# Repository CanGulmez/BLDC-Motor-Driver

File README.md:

# 2kW BLDC Motor Driver

This project was created for Teknofest - Efficiency Challenge Competition

This repository consists of two part. First is the motor dirver firmware
and second is the KiCAD design. In firmware development, I've used VS Code
and PlatformIO plugin. PCB design is based on STM32F44RE microcontroller
so that the firmware was written with STM32 HAL (Hardware Abstraction Layer)
library. KiCAD design includes both schematic and PCB layout so that it 
can be used directly.

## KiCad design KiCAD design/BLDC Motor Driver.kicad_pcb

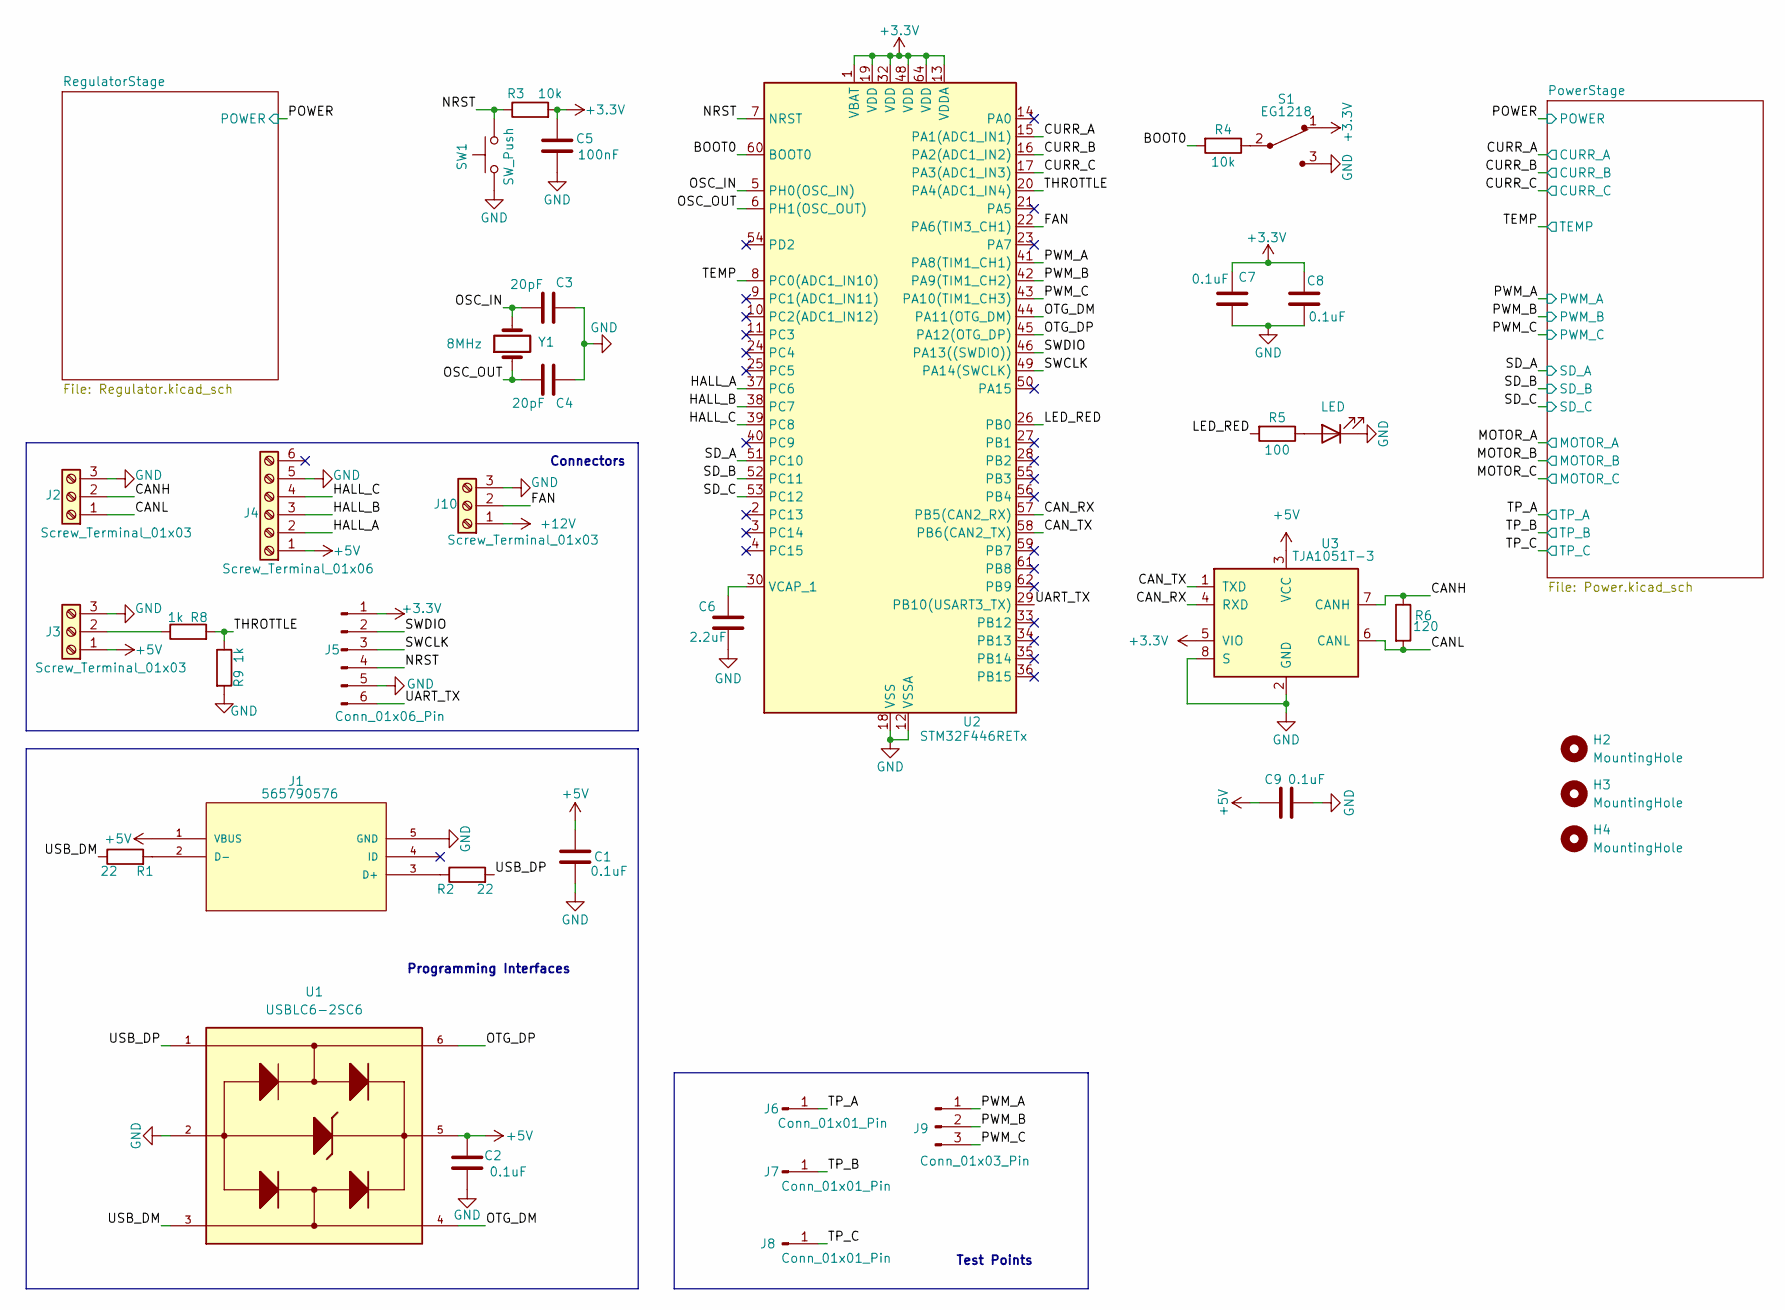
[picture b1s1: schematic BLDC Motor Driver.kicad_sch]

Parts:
C1, C2, C7, C8, C9: 0.1uF; C_0603_1608Metric
C3, C4: 20pF; C_0603_1608Metric
C5: 100nF; C_0603_1608Metric
C6: 2.2uF; C_0805_2012Metric
D1: LED; LED_0603_1608Metric
H2, H3, H4: MountingHole; MountingHole_3.2mm_M3
J1: 565790576; 56579-0576_MOL; MANUFACTURER_PART_NUMBER 565790576
J2, J3, J10: Screw_Terminal_01x03; TerminalBlock_Phoenix_MKDS-1,5-3-5.08_1x03_P5.08mm_Horizont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
J4: Screw_Terminal_01x06; TerminalBlock_Phoenix_MKDS-1,5-6-5.08_1x06_P5.08mm_Horizont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
J5: Conn_01x06_Pin; PinHeader_1x06_P2.54mm_Vertical
J6, J7, J8: Conn_01x01_Pin; PinHeader_1x01_P2.54mm_Vertical
J9: Conn_01x03_Pin; PinHeader_1x03_P2.54mm_Vertical
R1, R2: 22; R_0603_1608Metric
R3, R4: 10k; R_0603_1608Metric
R5: 100; R_0603_1608Metric
R6: 120; R_0603_1608Metric
R8, R9: 1k; R_0603_1608Metric
S1: EG1218; Switch_Slide_11.6x4mm_EG1218; MPN EG1218; Digi-Key_PN EG1903-ND
SW1: SW_Push; SW_SPST_B3U-1000P
U1: USBLC6-2SC6; SOT95P280X145-6N
U2: STM32F446RETx; LQFP-64_10x10mm_P0.5mm
U3: TJA1051T-3; SOIC-8_3.9x4.9mm_P1.27mm
Y1: 8MHz; Crystal_SMD_5032-2Pin_5.0x3.2mm

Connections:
+3.3V: C5.1, C7.1, C8.1, J5.1, R3.2, S1.1, U2.1 (VBAT), U2.13 (VDDA), U2.19 (VDD), U2.32 (VDD), U2.48 (VDD), U2.64 (VDD), U3.5 (VIO); also elsewhere on the board
+5V: C1.1, C2.1, C9.1, J1.1 (VBUS), J3.1, J4.1, U1.5, U3.3 (VCC); also elsewhere on the board
+12V: J10.1; also elsewhere on the board
/BOOT0: R4.2, U2.60 (BOOT0)
/CANH: J2.2, R6.1, U3.7 (CANH)
/CANL: J2.1, R6.2, U3.6 (CANL)
/CAN_RX: U2.57 (PB5(CAN2_RX)), U3.4 (RXD)
/CAN_TX: U2.58 (PB6(CAN2_TX)), U3.1 (TXD)
/CURR_A: U2.15 (PA1(ADC1_IN1)); also elsewhere on the board
/CURR_B: U2.16 (PA2(ADC1_IN2)); also elsewhere on the board
/CURR_C: U2.17 (PA3(ADC1_IN3)); also elsewhere on the board
/FAN: J10.2, U2.22 (PA6(TIM3_CH1))
/HALL_A: J4.2, U2.37 (PC6)
/HALL_B: J4.3, U2.38 (PC7)
/HALL_C: J4.4, U2.39 (PC8)
/LED_RED: R5.2, U2.26 (PB0)
/NRST: J5.4, R3.1, SW1.2, U2.7 (NRST)
/OSC_IN: C3.1, U2.5 (PH0(OSC_IN)), Y1.2
/OSC_OUT: C4.1, U2.6 (PH1(OSC_OUT)), Y1.1
/OTG_DM: U1.4, U2.44 (PA11(OTG_DM))
/OTG_DP: U1.6, U2.45 (PA12(OTG_DP))
/PWM_A: J9.1, U2.41 (PA8(TIM1_CH1)); also elsewhere on the board
/PWM_B: J9.2, U2.42 (PA9(TIM1_CH2)); also elsewhere on the board
/PWM_C: J9.3, U2.43 (PA10(TIM1_CH3)); also elsewhere on the board
/SD_A: U2.51 (PC10); also elsewhere on the board
/SD_B: U2.52 (PC11); also elsewhere on the board
/SD_C: U2.53 (PC12); also elsewhere on the board
/SWCLK: J5.3, U2.49 (PA14(SWCLK))
/SWDIO: J5.2, U2.46 (PA13((SWDIO)))
/TEMP: U2.8 (PC0(ADC1_IN10)); also elsewhere on the board
/THROTTLE: R8.2, R9.1, U2.20 (PA4(ADC1_IN4))
/TP_A: J6.1; also elsewhere on the board
/TP_B: J7.1; also elsewhere on the board
/TP_C: J8.1; also elsewhere on the board
/UART_TX: J5.6, U2.29 (PB10(USART3_TX))
/USB_DM: R1.1, U1.3
/USB_DP: R2.2, U1.1
GND: C1.2, C2.2, C3.2, C4.2, C5.2, C6.2, C7.2, C8.2, C9.2, D1.1 (K), J1.5 (GND), J2.3, J3.3, J4.5, J5.5, J10.3, R9.2, S1.3, SW1.1, U1.2, U2.12 (VSSA), U2.18 (VSS), U2.31 (VSS), U2.47 (VSS), U2.63 (VSS), U3.2 (GND), U3.8 (S); also elsewhere on the board
unnamed: D1.2 (A), R5.1
unnamed: J1.3 (D+), R2.1
unnamed: J1.2 (D-), R1.2
unnamed: J3.2, R8.1
unnamed: R4.1, S1.2
unnamed: C6.1, U2.30 (VCAP_1)

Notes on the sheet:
Connectors
Test Points
Programming Interfaces

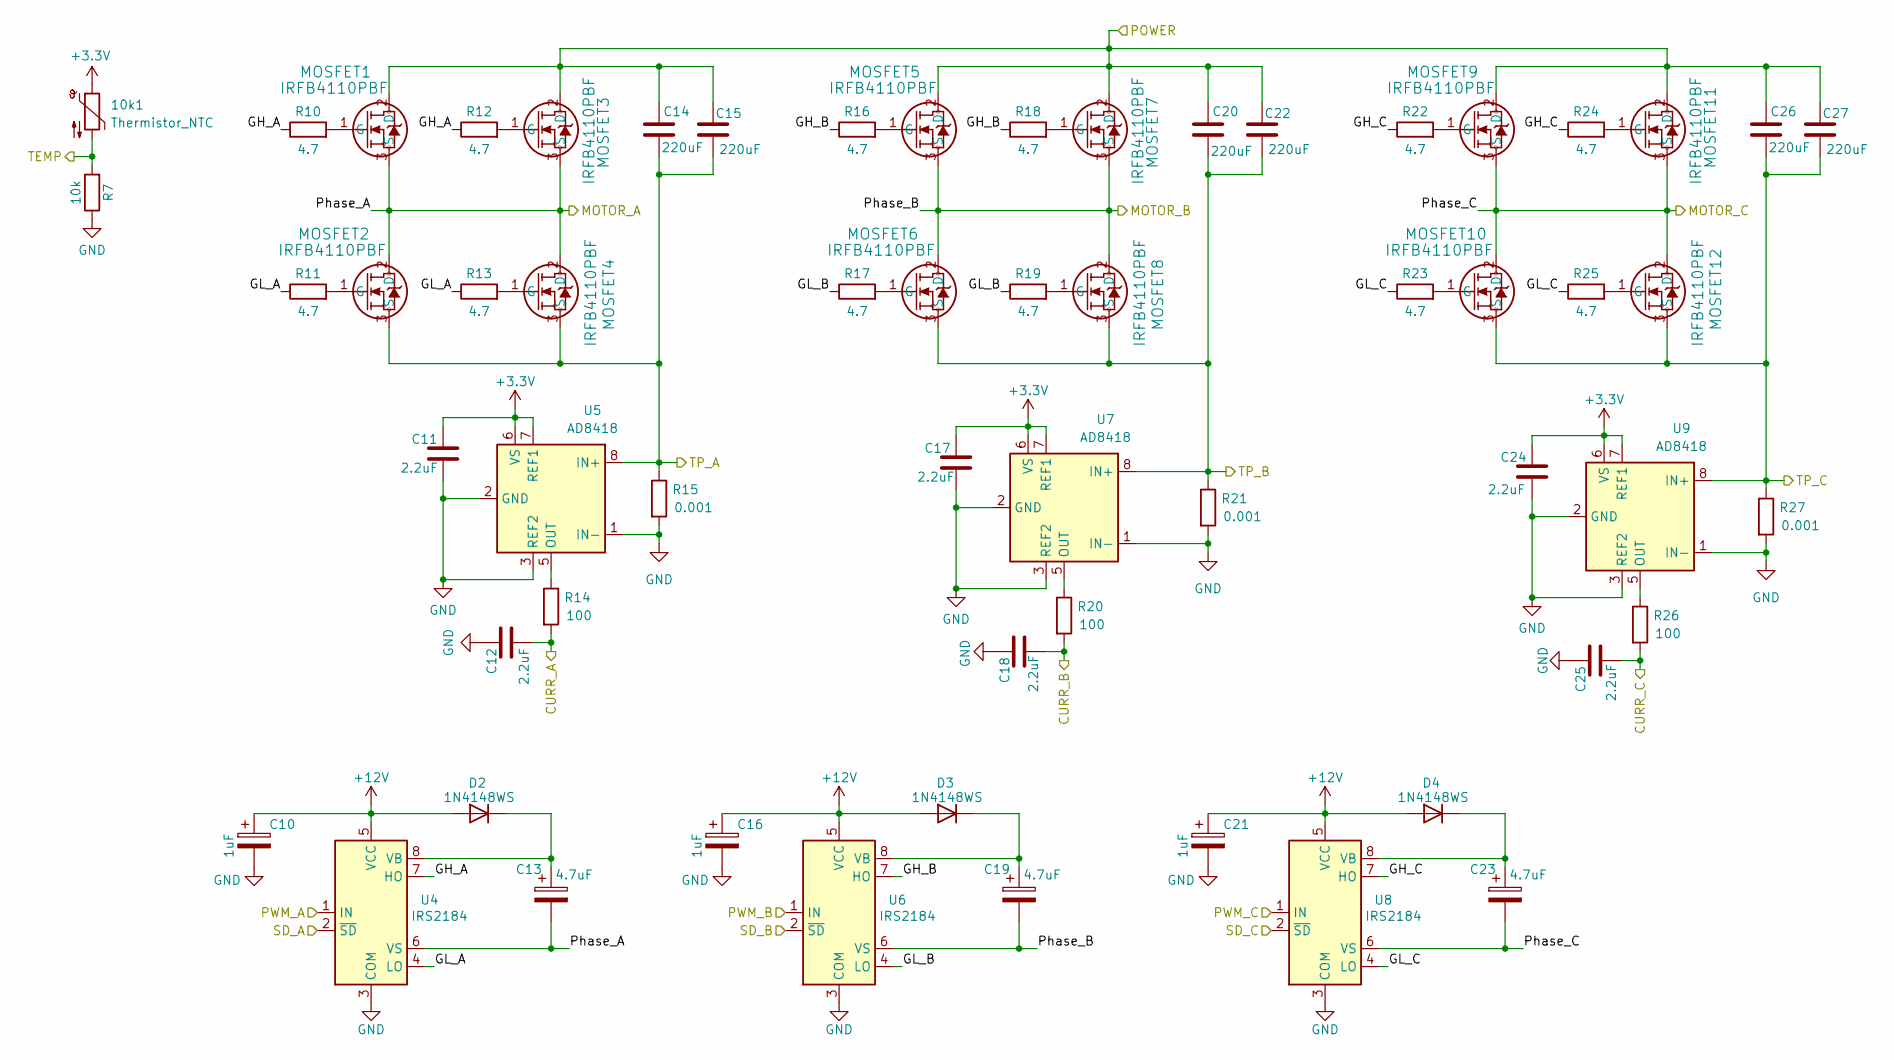
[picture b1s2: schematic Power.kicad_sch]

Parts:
10k1: Thermistor_NTC; R_0805_2012Metric
C10, C16, C21: 1uF; C_0805_2012Metric
C11, C12, C17, C18, C24, C25: 2.2uF; C_0805_2012Metric
C13, C19, C23: 4.7uF; C_0805_2012Metric
C14, C15, C20, C22, C26, C27: 220uF; C_Elec_10x10.2
D2, D3, D4: 1N4148WS; D_SOD-323
MOSFET1, MOSFET2, MOSFET3, MOSFET4, MOSFET5, MOSFET6, MOSFET7, MOSFET8, MOSFET9, MOSFET10, MOSFET11, MOSFET12: IRFB4110PBF; TO-220-3_Vertical
R7: 10k; R_0603_1608Metric
R10, R11, R12, R13, R16, R17, R18, R19, R22, R23, R24, R25: 4.7; R_0603_1608Metric
R14, R20, R26: 100; R_0603_1608Metric
R15, R21, R27: 0.001; R_2512_6332Metric
U4, U6, U8: IRS2184; SOIC-8_3.9x4.9mm_P1.27mm
U5, U7, U9: AD8418; SOIC-8_3.9x4.9mm_P1.27mm

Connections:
+3.3V: 10k1.1, C11.1, C17.1, C24.1, U5.6 (VS), U5.7 (REF1), U7.6 (VS), U7.7 (REF1), U9.6 (VS), U9.7 (REF1); also elsewhere on the board
+12V: C10.1, C16.1, C21.1, D2.2 (A), D3.2 (A), D4.2 (A), U4.5 (VCC), U6.5 (VCC), U8.5 (VCC); also elsewhere on the board
/CURR_A: C12.2, R14.2; also elsewhere on the board
/CURR_B: C18.2, R20.2; also elsewhere on the board
/CURR_C: C25.2, R26.2; also elsewhere on the board
/MOTOR_A: C13.2, MOSFET1.3 (S), MOSFET2.2 (D), MOSFET3.3 (S), MOSFET4.2 (D), U4.6 (VS)
/MOTOR_B: C19.2, MOSFET5.3 (S), MOSFET6.2 (D), MOSFET7.3 (S), MOSFET8.2 (D), U6.6 (VS)
/MOTOR_C: C23.2, MOSFET9.3 (S), MOSFET10.2 (D), MOSFET11.3 (S), MOSFET12.2 (D), U8.6 (VS)
/POWER: C14.1, C15.1, C20.1, C22.1, C26.1, C27.1, MOSFET1.2 (D), MOSFET3.2 (D), MOSFET5.2 (D), MOSFET7.2 (D), MOSFET9.2 (D), MOSFET11.2 (D); also elsewhere on the board
/PWM_A: U4.1 (IN); also elsewhere on the board
/PWM_B: U6.1 (IN); also elsewhere on the board
/PWM_C: U8.1 (IN); also elsewhere on the board
/PowerStage/GH_A: R10.1, R12.1, U4.7 (HO)
/PowerStage/GH_B: R16.1, R18.1, U6.7 (HO)
/PowerStage/GH_C: R22.1, R24.1, U8.7 (HO)
/PowerStage/GL_A: R11.1, R13.1, U4.4 (LO)
/PowerStage/GL_B: R17.1, R19.1, U6.4 (LO)
/PowerStage/GL_C: R23.1, R25.1, U8.4 (LO)
/SD_A: U4.2 (~SD); also elsewhere on the board
/SD_B: U6.2 (~SD); also elsewhere on the board
/SD_C: U8.2 (~SD); also elsewhere on the board
/TEMP: 10k1.2, R7.2; also elsewhere on the board
/TP_A: C14.2, C15.2, MOSFET2.3 (S), MOSFET4.3 (S), R15.1, U5.8 (IN+); also elsewhere on the board
/TP_B: C20.2, C22.2, MOSFET6.3 (S), MOSFET8.3 (S), R21.1, U7.8 (IN+); also elsewhere on the board
/TP_C: C26.2, C27.2, MOSFET10.3 (S), MOSFET12.3 (S), R27.1, U9.8 (IN+); also elsewhere on the board
GND: C10.2, C11.2, C12.1, C16.2, C17.2, C18.1, C21.2, C24.2, C25.1, R7.1, R15.2, R21.2, R27.2, U4.3 (COM), U5.1 (IN-), U5.2 (GND), U5.3 (REF2), U6.3 (COM), U7.1 (IN-), U7.2 (GND), U7.3 (REF2), U8.3 (COM), U9.1 (IN-), U9.2 (GND), U9.3 (REF2); also elsewhere on the board
unnamed: C13.1, D2.1 (K), U4.8 (VB)
unnamed: C19.1, D3.1 (K), U6.8 (VB)
unnamed: C23.1, D4.1 (K), U8.8 (VB)
unnamed: MOSFET1.1 (G), R10.2
unnamed: MOSFET2.1 (G), R11.2
unnamed: MOSFET3.1 (G), R12.2
unnamed: MOSFET4.1 (G), R13.2
unnamed: MOSFET5.1 (G), R16.2
unnamed: MOSFET6.1 (G), R17.2
unnamed: MOSFET7.1 (G), R18.2
unnamed: MOSFET8.1 (G), R19.2
unnamed: MOSFET9.1 (G), R22.2
unnamed: MOSFET10.1 (G), R23.2
unnamed: MOSFET11.1 (G), R24.2
unnamed: MOSFET12.1 (G), R25.2
unnamed: R14.1, U5.5 (OUT)
unnamed: R20.1, U7.5 (OUT)
unnamed: R26.1, U9.5 (OUT)

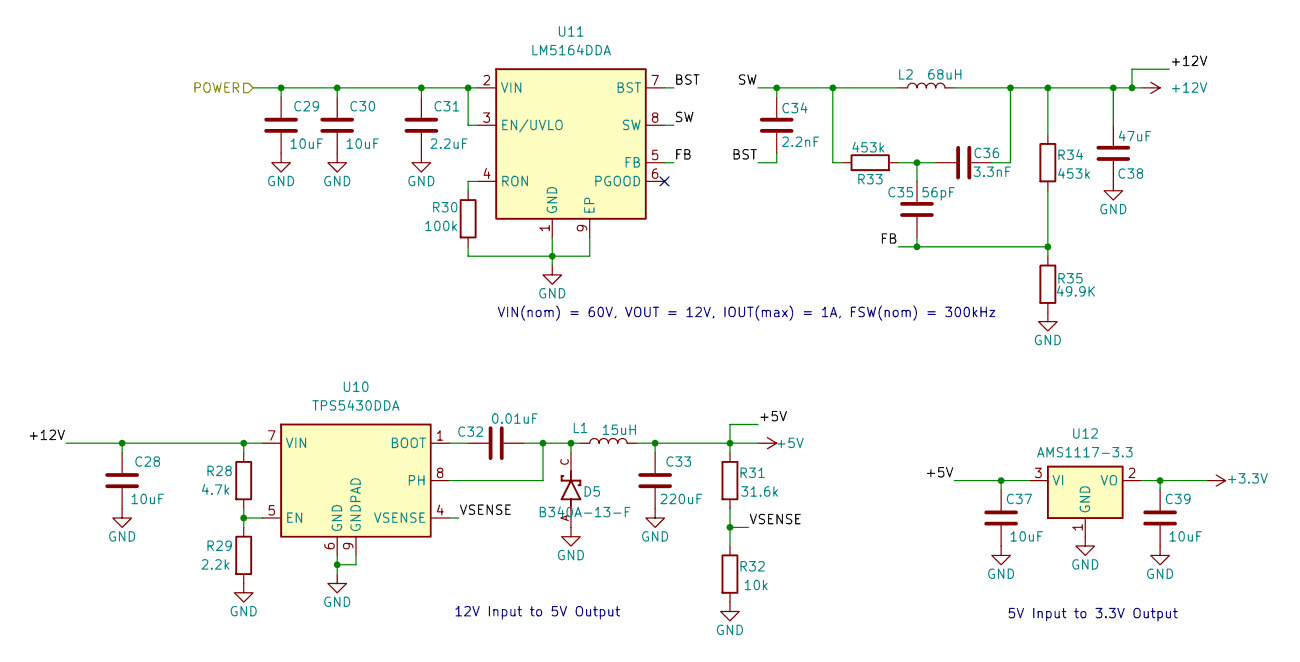
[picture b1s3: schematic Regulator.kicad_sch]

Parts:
C28, C29, C30, C37, C39: 10uF; C_0805_2012Metric
C31: 2.2uF; C_0805_2012Metric
C32: 0.01uF; C_0402_1005Metric
C33: 220uF; C_Elec_6.3x5.4
C34: 2.2nF; C_0402_1005Metric
C35: 56pF; C_0402_1005Metric
C36: 3.3nF; C_0402_1005Metric
C38: 47uF; C_Elec_8x6.2
D5: B340A-13-F; DIOM5226X240N; PARTREV 17-2
L1: 15uH; L_0805_2012Metric
L2: 68uH; L_6.3x6.3_H3
R28: 4.7k; R_0603_1608Metric
R29: 2.2k; R_0603_1608Metric
R30: 100k; R_0603_1608Metric
R31: 31.6k; R_0603_1608Metric
R32: 10k; R_0603_1608Metric
R33, R34: 453k; R_0603_1608Metric
R35: 49.9K; R_0603_1608Metric
U10: TPS5430DDA; TI_SO-PowerPAD-8_ThermalVias
U11: LM5164DDA; HSOP-8-1EP_3.9x4.9mm_P1.27mm_EP2.41x3.1mm_ThermalVias
U12: AMS1117-3.3; SOT-223-3_TabPin2

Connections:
+3.3V: C39.1, U12.2 (VO); also elsewhere on the board
+5V: C33.1, C37.1, L1.2, R31.1, U12.3 (VI); also elsewhere on the board
+12V: C28.1, C36.2, C38.2, L2.2, R28.1, R34.1, U10.7 (VIN); also elsewhere on the board
/POWER: C29.1, C30.1, C31.1, U11.2 (VIN), U11.3 (EN/UVLO); also elsewhere on the board
/RegulatorStage/BST: C34.2, U11.7 (BST)
/RegulatorStage/FB: C35.1, R34.2, R35.1, U11.5 (FB)
/RegulatorStage/SW: C34.1, L2.1, R33.1, U11.8 (SW)
/RegulatorStage/VSENSE: R31.2, R32.1, U10.4 (VSENSE)
GND: C28.2, C29.2, C30.2, C31.2, C33.2, C37.2, C38.1, C39.2, D5.A, R29.2, R30.2, R32.2, R35.2, U10.6 (GND), U10.9 (GNDPAD), U11.1 (GND), U11.9 (EP), U12.1 (GND); also elsewhere on the board
unnamed: C35.2, C36.1, R33.2
unnamed: C32.1, U10.1 (BOOT)
unnamed: R28.2, R29.1, U10.5 (EN)
unnamed: C32.2, D5.C, L1.1, U10.8 (PH)
unnamed: R30.1, U11.4 (RON)

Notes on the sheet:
VIN(nom) = 60V, VOUT = 12V, IOUT(max) = 1A, FSW(nom) = 300kHz
5V Input to 3.3V Output
12V Input to 5V Output

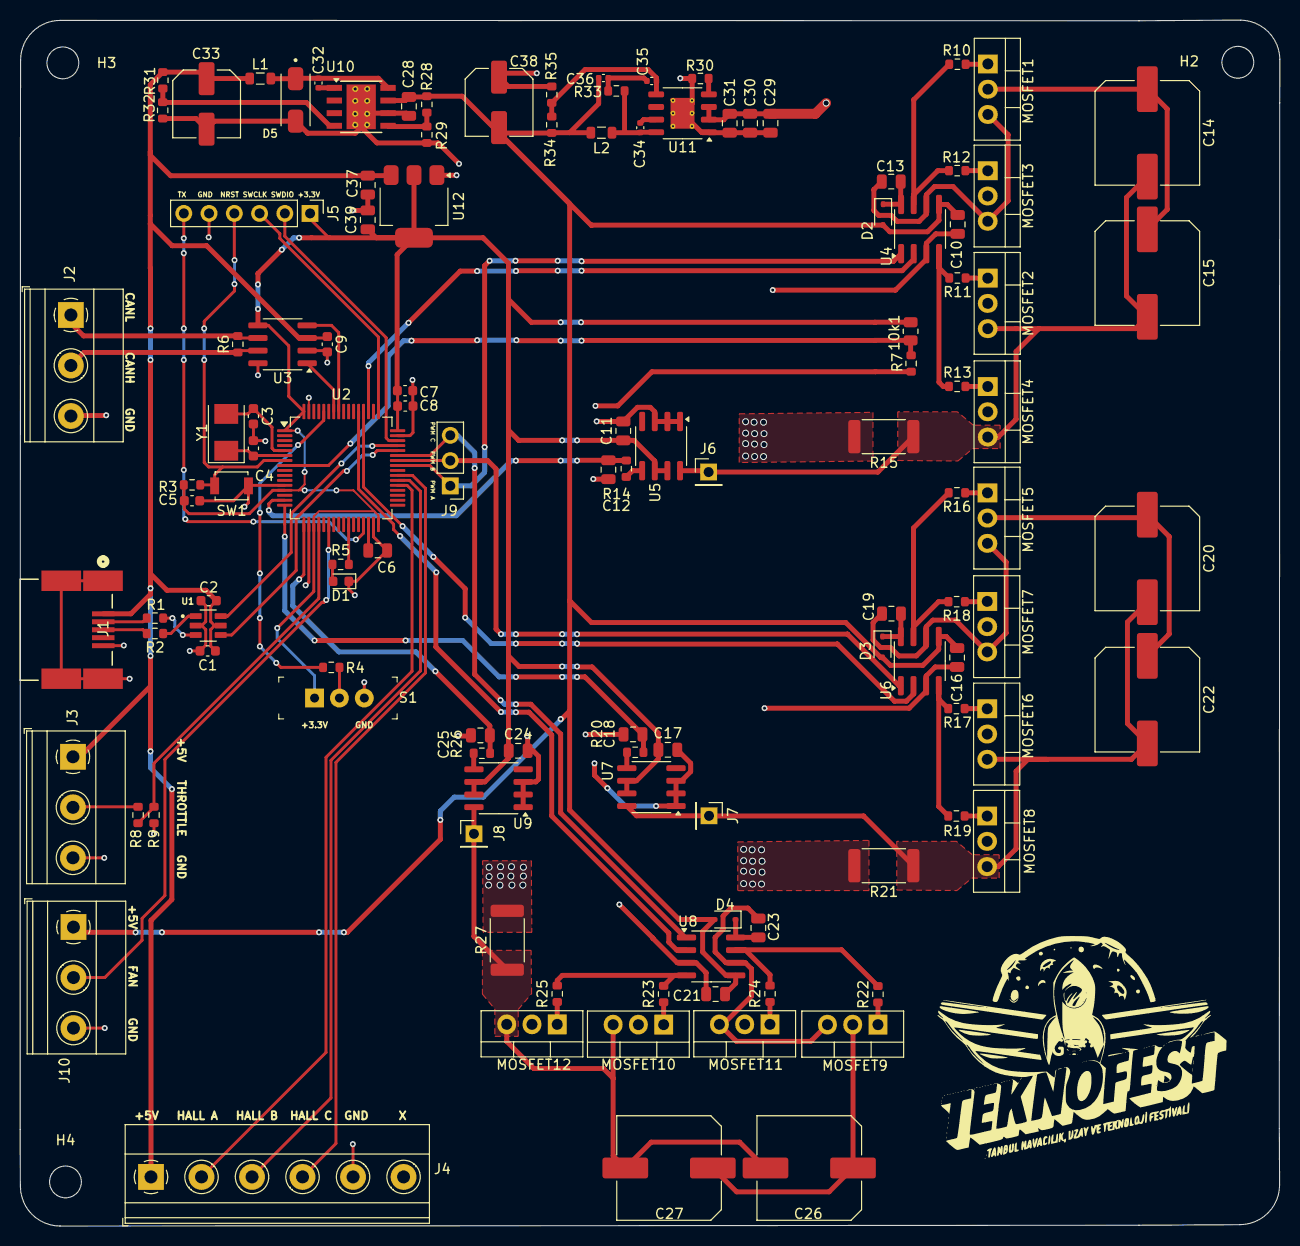
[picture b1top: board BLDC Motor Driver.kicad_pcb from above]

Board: 2 copper layers, 126.7 x 121.3 mm, 122 parts (0 on the bottom side), 81 nets.

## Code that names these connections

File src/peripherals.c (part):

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 * BLDC Motor Driver Peripheral Configurations 
 * 
 * Peripherals:      GPIOA, GPIOB, GPIOC, ADC1, TIM2, DMA1, CAN2
 * Requests:         NRST, BOOT0, PH0(OSC_IN), PH1(OSC_OUT), PC0(ADC1_IN10),
 *                   PC1(ADC1_IN11), PC2(ADC1_IN12), PA1(ADC1_IN1), 
 *                   PA2(ADC1_IN2), PA3(ADC1_IN3), PC4(PGOOD), PC6(HALL_A),
 *                   PC7(HALL_B), PC8(HALL_C), PB0(LED_RED), PC10(SD_A),
 *                   PC11(SD_B), PC12(SD_C), PB5(CAN2_RX), PB6(CAN2_TX),
 *                   PA8(TIM1_CH1), PA9(TIM1_CH2), PA10(TIM1_CH3), 
 *                   PA11(OTG_DM), PA12(OTG_DP), PA13(SWDIO), PA14(SWCLK)
 */

#include "bldc_motor_driver.h"
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 * Analog-to-Digital Converter Configuration
 * 
 * Peripheral:       ADC1
 * Requests:         PA1(ADC1_IN1), PA2(ADC1_IN2), PA3(ADC1_IN3),
 *                   PA4(ADC1_IN4), PC0(ADC1_IN10)
 * 
 * Set the ADC peripheral to read phase currents and
 * temperature sensors.
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   HAL_ADC_Init(&hadc1);

   uint32_t channels[5] = {
      ADC_CHANNEL_1,          // PA1
      ADC_CHANNEL_2,          // PA2
      ADC_CHANNEL_3,          // PA3
      ADC_CHANNEL_4,          // PA4
      ADC_CHANNEL_10          // PC0 
  };
  for (int i = 0; i < 5; i++) {
      sConfig.Channel = channels[i];
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 * Digital Input/Output Configuration
 * 
 * Peripherals:      GPIOA, GPIOB, GPIOC
 * Requests:         PB0(LED_RED), PC10(SD_A), PC11(SD_B), 
 *                   PC12(SD_C), PC6(HALL_A), PC7(HALL_B), 
 *                   PC8(HALL_C), PA8(TIM1_CH1), PA9(TIM1_CH2),
 *                   PA10(TIM1_CH3)
 * 
 * Set the digital input/output modes.
 */
void bldc_perip_digital(void)
{
   /* PC10(SD_A), PC11(SD_B), PC12(SD_C) */
   igpio.Pin = GPIO_PIN_10 | GPIO_PIN_11 | GPIO_PIN_12;
   igpio.Mode = GPIO_MODE_OUTPUT_PP;
   igpio.Pull = GPIO_NOPULL;
   igpio.Speed = GPIO_SPEED_FREQ_HIGH;
   HAL_GPIO_Init(GPIOC, &igpio);
   
   /* PB0(LED_RED) */
   igpio.Pin = GPIO_PIN_0;
   igpio.Mode = GPIO_MODE_OUTPUT_PP;
   igpio.Pull = GPIO_NOPULL;
   igpio.Speed = GPIO_SPEED_FREQ_HIGH;
   HAL_GPIO_Init(GPIOB, &igpio);

   /* PC6(HALL_A), PC7(HALL_B), PC8(HALL_C) */
   igpio.Pin = GPIO_PIN_6 | GPIO_PIN_7 | GPIO_PIN_8;
   igpio.Mode = GPIO_MODE_IT_RISING_FALLING; 
   igpio.Pull = GPIO_NOPULL;
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   HAL_NVIC_SetPriority(EXTI9_5_IRQn, 0, 0);
   HAL_NVIC_EnableIRQ(EXTI9_5_IRQn);

   /* PA8(TIM1_CH1), PA9(TIM1_CH2), PA10(TIM1_CH3) */
   igpio.Pin = GPIO_PIN_8 | GPIO_PIN_9 | GPIO_PIN_10;
   igpio.Mode = GPIO_MODE_AF_PP;
   igpio.Pull = GPIO_NOPULL;
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   igpio.Alternate = GPIO_AF1_TIM1;
   HAL_GPIO_Init(GPIOA, &igpio);

   /* PB5(CAN2_RX), PB6(CAN2_TX) */
   igpio.Pin = GPIO_PIN_5 | GPIO_PIN_6;
   igpio.Mode = GPIO_MODE_AF_PP;
   igpio.Pull = GPIO_NOPULL;
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   igpio.Alternate = GPIO_AF9_CAN2;
   HAL_GPIO_Init(GPIOB, &igpio);

   /* PB10(USART3_TX) */
   igpio.Pin = GPIO_PIN_10;
   igpio.Mode = GPIO_MODE_AF_PP;
   igpio.Pull = GPIO_NOPULL;
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   igpio.Alternate = GPIO_AF7_USART3;
   HAL_GPIO_Init(GPIOB, &igpio);

   /* PA6(TIM3_CH1) */
   igpio.Pin = GPIO_PIN_6;
   igpio.Mode = GPIO_MODE_AF_PP;
   igpio.Pull = GPIO_NOPULL;
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 * Serial Line from MCU to Host Machine
 * 
 * Peripherals:      USART3
 * Requests:         PB10(USART3_TX)
 * 
 * Set the USART3 peripheral to communicate with the 
 * host machine over a serial line. The baud rate is 
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 * Data Transmission over CAN Bus
 * 
 * Peripherals:      CAN2
 * Requests:         PB5(CAN2_RX), PB6(CAN2_TX)
 * 
 * Baud Rate = APB1_CLK / (Prescalar + (1 + BS1 + BS2))
 * Set the CAN bus to receive/transmit data with 500Kbps.
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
